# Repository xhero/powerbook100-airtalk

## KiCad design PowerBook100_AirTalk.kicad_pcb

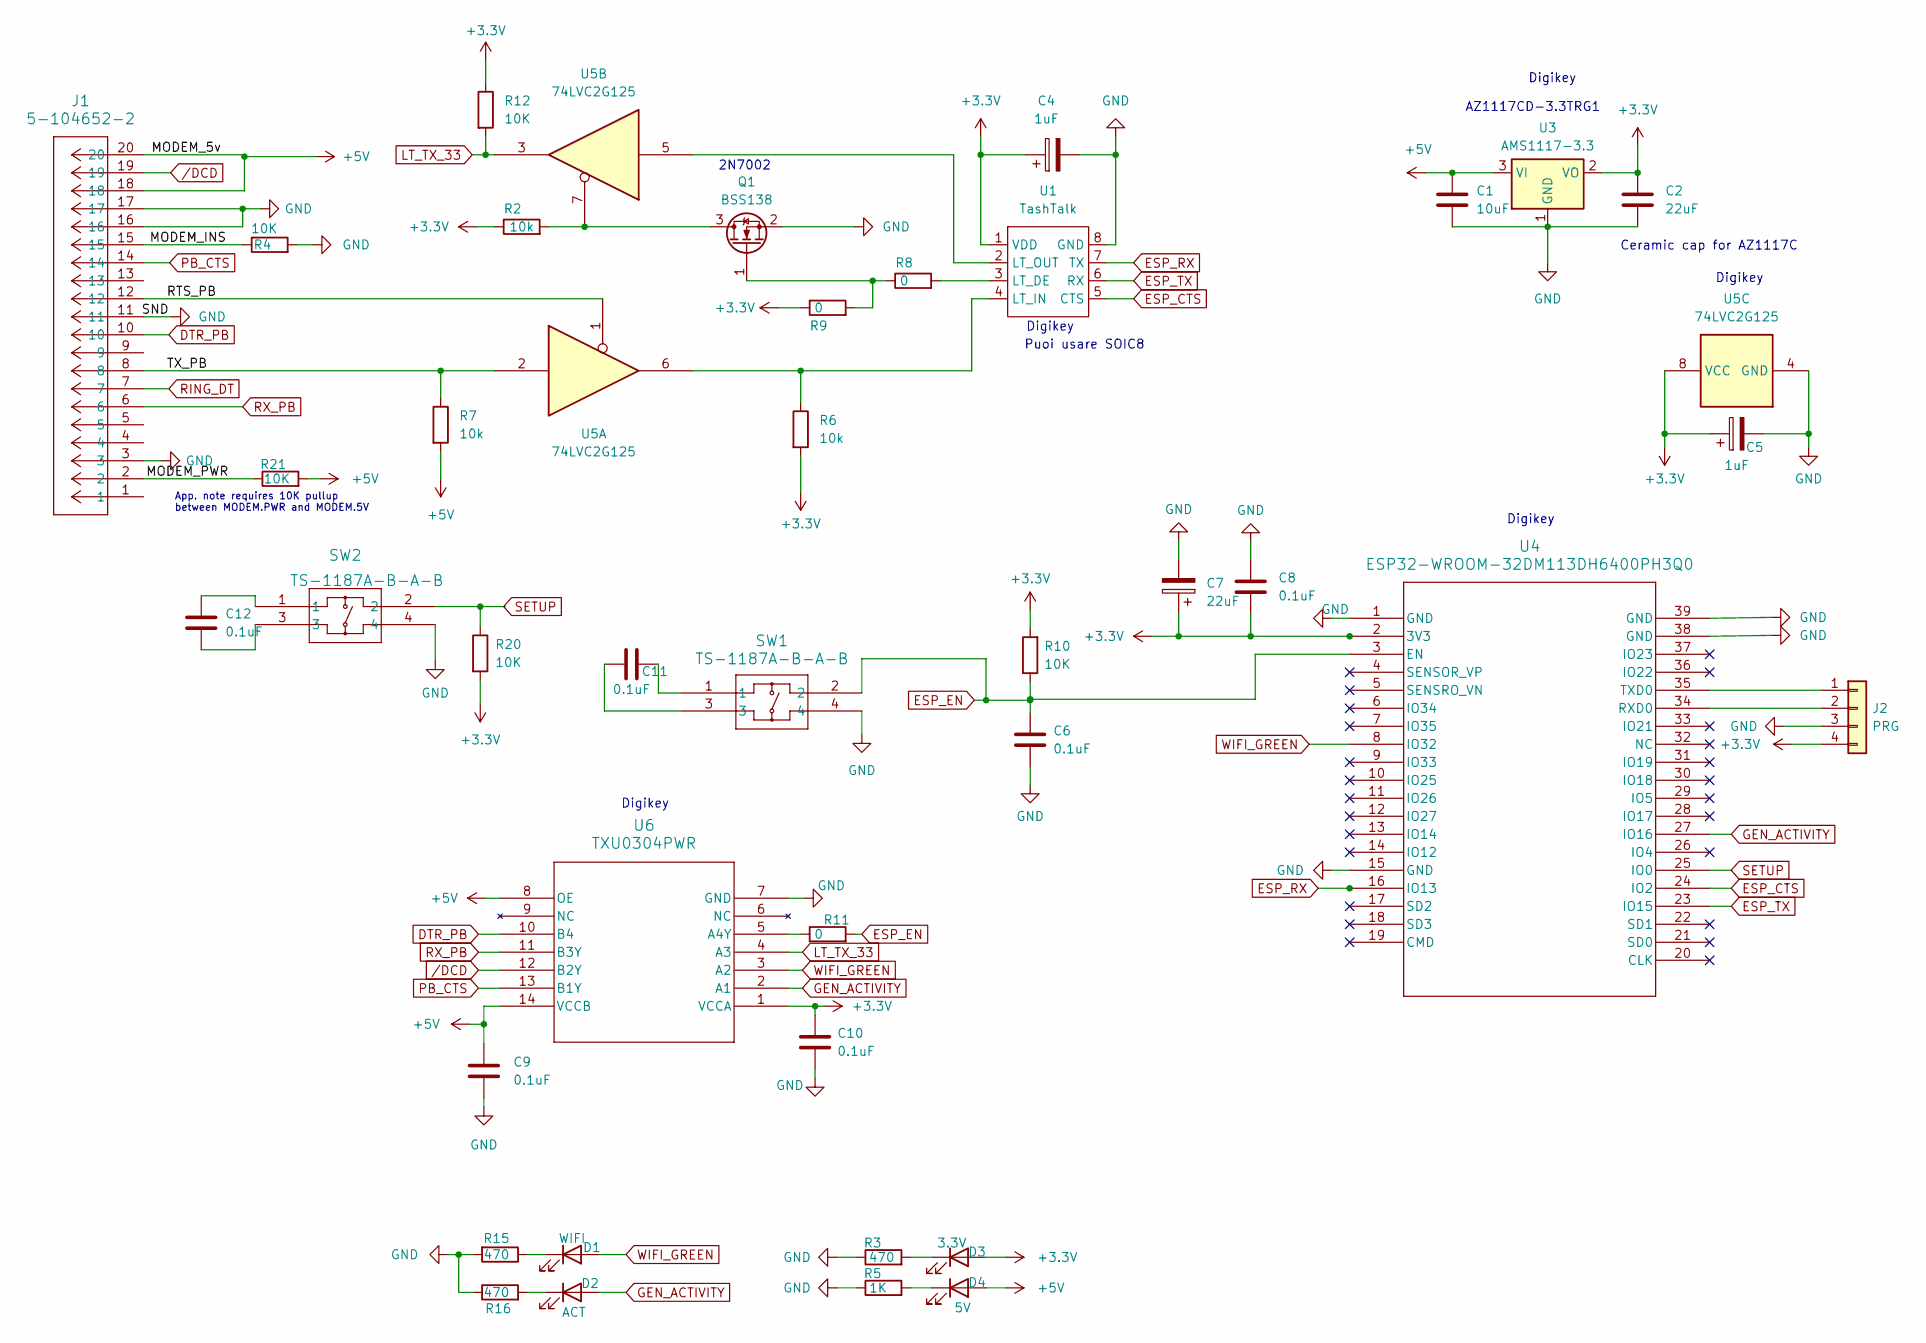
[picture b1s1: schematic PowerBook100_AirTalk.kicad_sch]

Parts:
C1: 10uF; C_0805_2012Metric
C2: 22uF; C_0805_2012Metric
C4, C5: 1uF; C_1206_3216Metric
C6, C8, C9, C10: 0.1uF; C_0805_2012Metric
C7: 22uF; C_1206_3216Metric
C11, C12: 0.1uF; C_1206_3216Metric
D1: WIFI; LED_0805_2012Metric
D2: ACT; LED_0805_2012Metric
D3: 3.3V; LED_0805_2012Metric
D4: 5V; LED_0805_2012Metric
J1: 5-104652-2; CONN_5-104652-2_TYCO
J2: PRG; PinHeader_1x04_P1.00mm_Vertical_SMD_Pin1Right
Q1: BSS138; SOT-23
R2, R6, R7: 10k; R_0805_2012Metric
R3, R15, R16: 470; R_0805_2012Metric
R4, R10, R12, R20, R21: 10K; R_0805_2012Metric
R5: 1K; R_0805_2012Metric
R8, R9, R11: 0; R_0805_2012Metric
SW1, SW2: TS-1187A-B-A-B; SW_Push_1P1T_XKB_TS-1187A
U1: TashTalk; SOIC-8_3.9x4.9mm_P1.27mm
U3: AMS1117-3.3; TO-252-3_TabPin2
U4: ESP32-WROOM-32DM113DH6400PH3Q0; ESP32-WROOM-32D
U5: 74LVC2G125; TSSOP-8_3x3mm_P0.65mm
U6: TXU0304PWR; TSSOP14_PW_TEX

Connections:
+3.3V: C2.1, C4.1, C5.1, C7.1, C8.2, C10.1, D3.2 (A), J2.4, R2.1, R6.2, R9.1, R10.2, R12.1, R20.2, U1.1 (VDD), U3.2 (VO), U4.2 (3V3), U5.8 (VCC), U6.1 (VCCA)
+5V: C1.1, C9.1, D4.2 (A), J1.18, J1.20, R7.2, R21.2, U3.3 (VI), U6.8 (OE), U6.14 (VCCB)
/MODEM_INS: J1.15, R4.1
/MODEM_PWR: J1.2, R21.1
/RTS_PB: J1.12, U5.1
/TX_PB: J1.8, R7.1, U5.2
DTR_PB: J1.10, U6.10 (B4)
ESP_CTS: U1.5 (CTS), U4.24 (IO2)
ESP_EN: C6.2, R10.1, R11.2, SW1.2, U4.3 (EN)
ESP_RX: U1.7 (TX), U4.16 (IO13)
ESP_TX: U1.6 (RX), U4.23 (IO15)
GEN_ACTIVITY: D2.2 (A), U4.27 (IO16), U6.2 (A1)
GND: C1.2, C2.2, C4.2, C5.2, C6.1, C7.2, C8.1, C9.2, C10.2, J1.3, J1.11, J1.16, J1.17, J2.3, Q1.2 (S), R3.1, R4.2, R5.1, R15.2, R16.1, SW1.4, SW2.4, U1.8 (GND), U3.1 (GND), U4.1 (GND), U4.15 (GND), U4.38 (GND), U4.39 (GND), U5.4 (GND), U6.7 (GND)
LT_TX_33: R12.2, U5.3, U6.4 (A3)
unnamed: C11.1, SW1.3
unnamed: C11.2, SW1.1
unnamed: C12.1, SW2.1
unnamed: C12.2, SW2.3
unnamed: D1.1 (K), R15.1
unnamed: D2.1 (K), R16.2
unnamed: D3.1 (K), R3.2
unnamed: D4.1 (K), R5.2
unnamed: J2.1, U4.35 (TXD0)
unnamed: J2.2, U4.34 (RXD0)
unnamed: Q1.3 (D), R2.2, U5.7
unnamed: Q1.1 (G), R8.1, R9.2
unnamed: R8.2, U1.3 (LT_DE)
unnamed: R6.1, U1.4 (LT_IN), U5.6
unnamed: U1.2 (LT_OUT), U5.5
unnamed: R11.1, U6.5 (A4Y)
PB_CTS: J1.14, U6.13 (B1Y)
RING_DT: J1.7
RX_PB: J1.6, U6.11 (B3Y)
SETUP: R20.1, SW2.2, U4.25 (IO0)
WIFI_GREEN: D1.2 (A), U4.8 (IO32), U6.3 (A2)
/DCD: J1.19, U6.12 (B2Y)

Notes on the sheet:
Digikey
Puoi usare SOIC8
App. note requires 10K pullup between MODEM.PWR and MODEM.5V
AZ1117CD-3.3TRG1
2N7002
Ceramic cap for AZ1117C

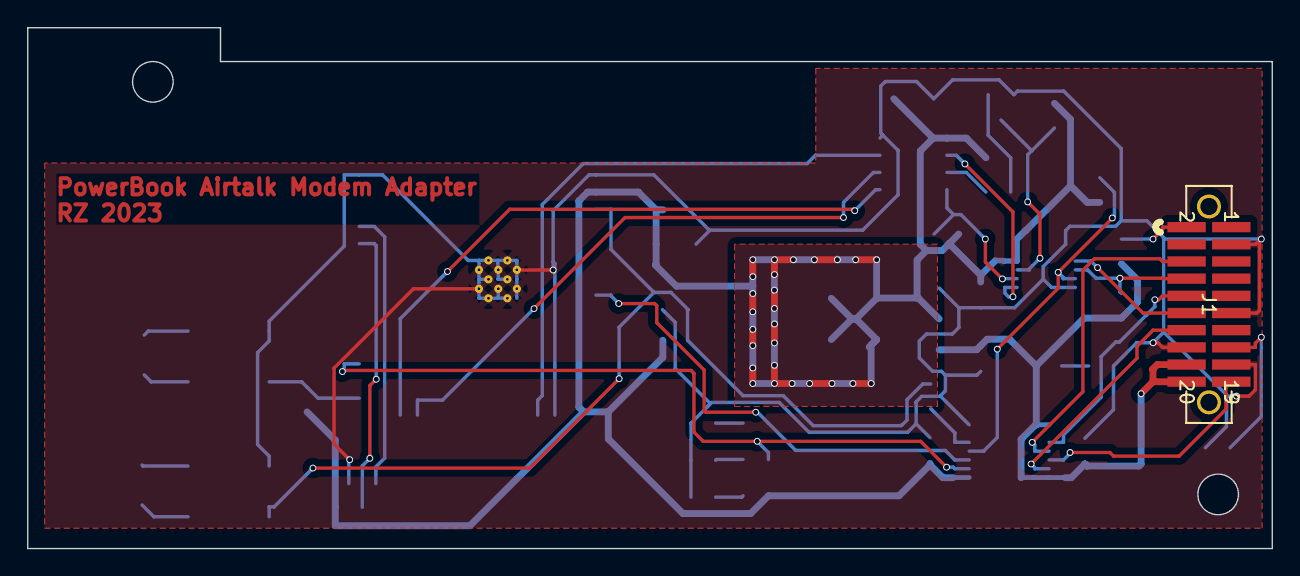
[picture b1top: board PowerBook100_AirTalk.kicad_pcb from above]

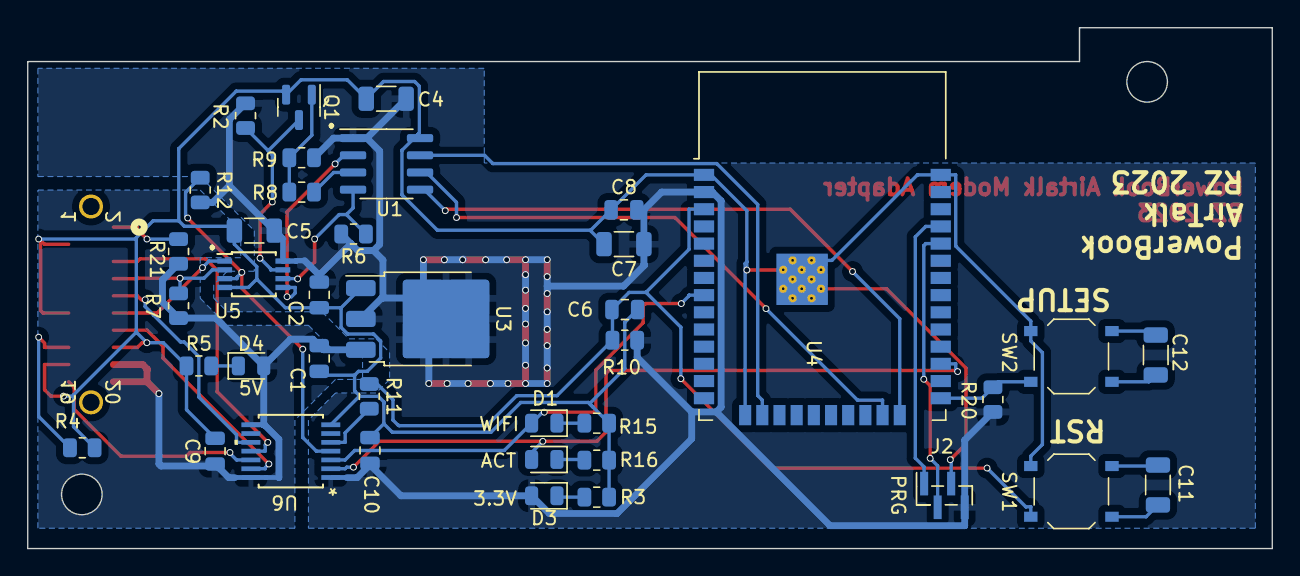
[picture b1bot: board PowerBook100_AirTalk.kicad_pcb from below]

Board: 2 copper layers, 92.0 x 38.5 mm, 40 parts (39 on the bottom side), 35 nets.

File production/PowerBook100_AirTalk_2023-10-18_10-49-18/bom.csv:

"Designator","Footprint","Quantity","Value","LCSC Part #"
"C1",805,1,"10uF","C15850"
"C10, C6, C8, C9",805,4,"0.1uF","C49678"
"C11, C12",1206,2,"0.1uF","C24497"
"C2",805,1,"22uF","C45783"
"C4, C5",1206,2,"1uF","C1848"
"C7",1206,1,"22uF","C12891"
"D1",805,1,"WIFI","C2296"
"D2",805,1,"ACT","C2296"
"D3",805,1,"3.3V","C84256"
"D4",805,1,"5V","C84256"
"J1","CONN_5-104652-2_TYCO",1,"5-104652-2",
"J2","PinHeader_1x04_P1.00mm_Vertical_SMD_Pin1Right",1,"PRG",
"Q1","SOT-23",1,"BSS138","C8545"
"R10, R12, R2, R20, R21, R4, R6, R7",805,8,"10K","C17414"
"R11, R8, R9",805,3,0,
"R15, R16, R3",805,3,470,"C17710"
"R5",805,1,"1K","C17513"
"SW1, SW2","SW_Push_1P1T_XKB_TS-1187A",2,"TS-1187A-B-A-B","C318884"
"U1","SOIC-8_3.9x4.9mm_P1.27mm",1,"TashTalk",
"U3","TO-252-3_TabPin2",1,"AMS1117-3.3",
"U4","ESP32-WROOM-32D",1,"ESP32-WROOM-32DM113DH6400PH3Q0",
"U5","TSSOP-8_3x3mm_P0.65mm",1,"74LVC2G125",
"U6","TSSOP14_PW_TEX",1,"TXU0304PWR",

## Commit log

2023-08-12 New files
2023-08-16 More mods
2023-08-29 Add PCB layout
2023-09-03 Add proper dimensions
2023-09-03 Add cdev and init source
2023-10-18 New revision
2023-10-18 Add production files for v2
2024-02-11 Add footprint
2024-08-16 Initial version 1.1
